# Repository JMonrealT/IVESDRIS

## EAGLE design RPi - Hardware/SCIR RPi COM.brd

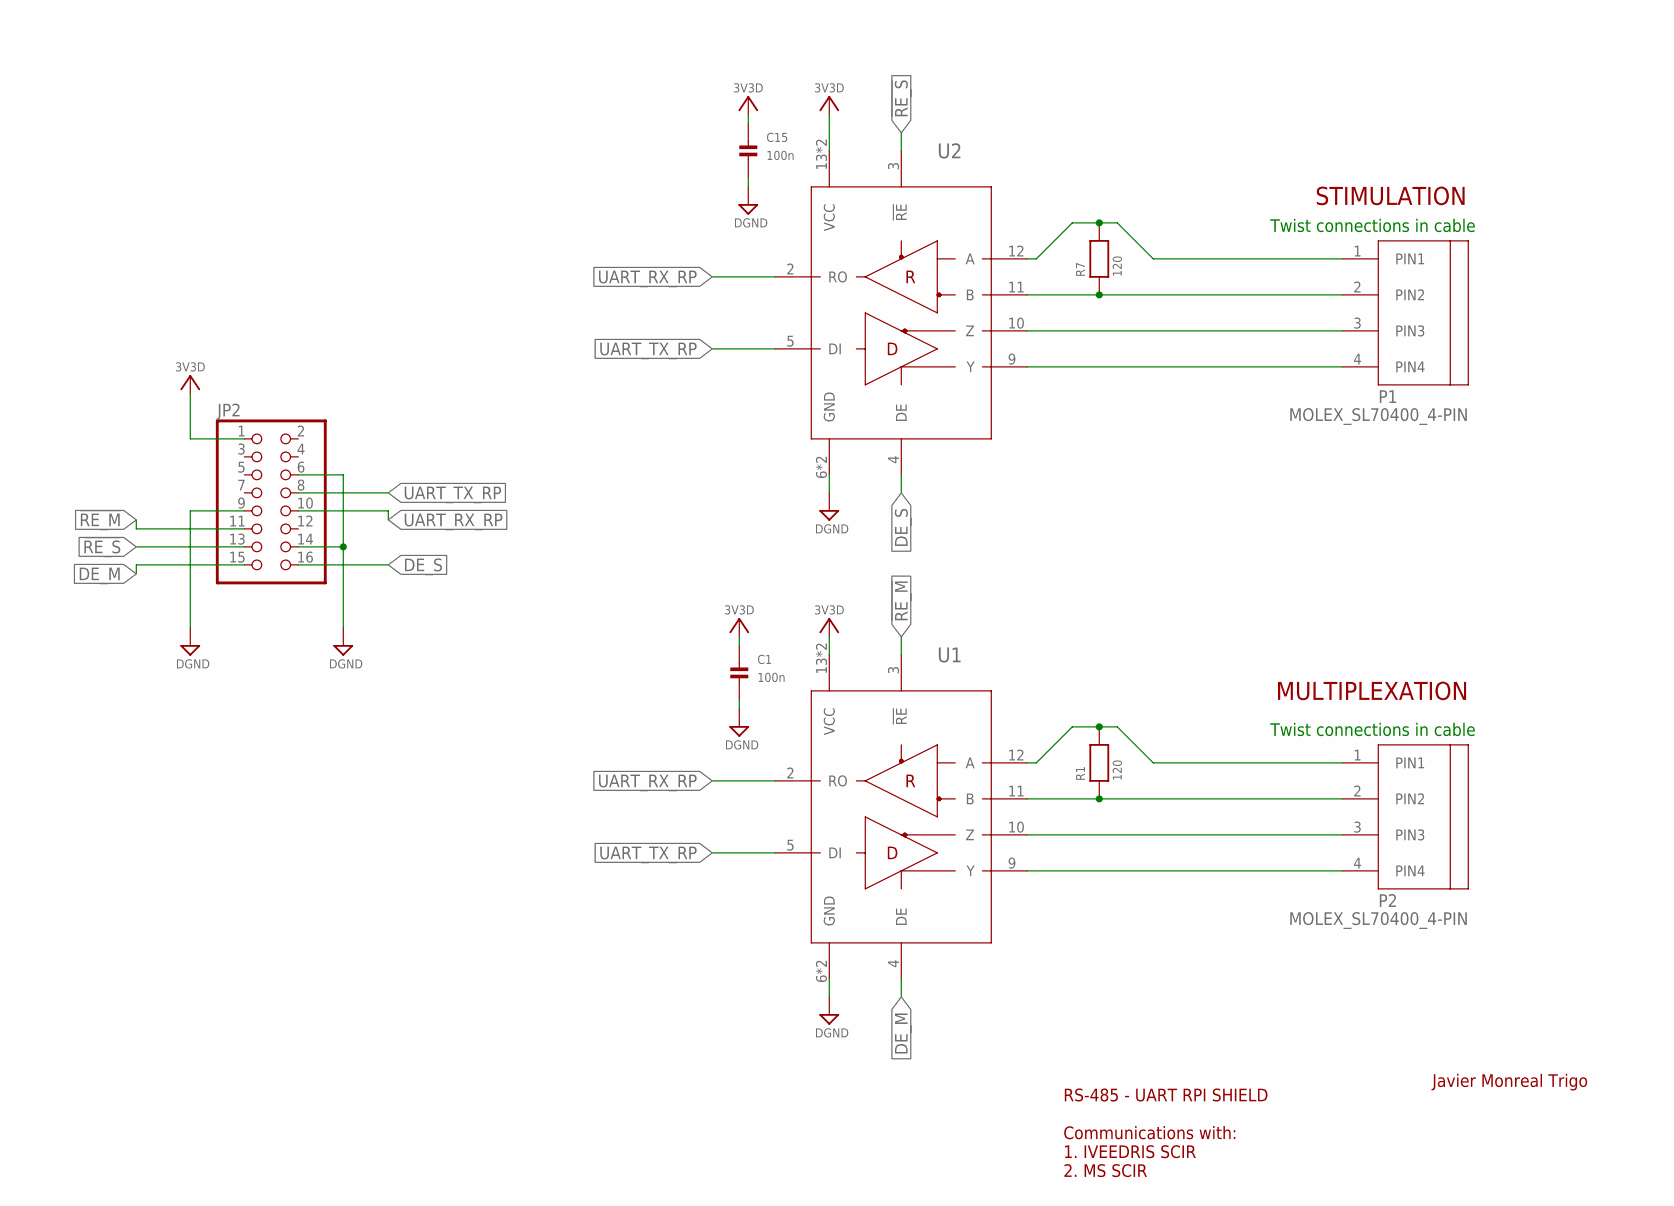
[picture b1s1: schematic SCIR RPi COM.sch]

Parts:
C1, C15: 100n; 0805
JP2: HEADER-2X8; 2X08
P1, P2: MOLEX_SL70400_4-PIN
R1, R7: 120; 0805
U1, U2: MAX3491ECSD+; SO14

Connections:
3V3D: C1.1, C15.1, JP2.1, U1.13 (VCC), U1.14 (VCC), U2.13 (VCC), U2.14 (VCC)
!RE_M: JP2.11, U1.3 (!RE)
!RE_S: JP2.13, U2.3 (!RE)
DE_M: JP2.15, U1.4 (DE)
DE_S: JP2.16, U2.4 (DE)
DGND: C1.2, C15.2, JP2.6, JP2.9, JP2.14, U1.6 (GND), U1.7 (GND), U2.6 (GND), U2.7 (GND)
unnamed: P1.1 (PIN1), R7.2, U2.12 (A)
unnamed: P2.2 (PIN2), R1.1, U1.11 (B)
unnamed: P1.3 (PIN3), U2.10 (Z)
unnamed: P2.1 (PIN1), R1.2, U1.12 (A)
unnamed: P1.4 (PIN4), U2.9 (Y)
unnamed: P2.4 (PIN4), U1.9 (Y)
unnamed: P2.3 (PIN3), U1.10 (Z)
unnamed: P1.2 (PIN2), R7.1, U2.11 (B)
UART_RX_RP: JP2.10, U1.2 (RO), U2.2 (RO)
UART_TX_RP: JP2.8, U1.5 (DI), U2.5 (DI)

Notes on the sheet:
RS-485 - UART RPI SHIELD Communications with: 1. IVEEDRIS SCIR 2. MS SCIR
Twist connections in cable
Javier Monreal Trigo
STIMULATION
MULTIPLEXATION

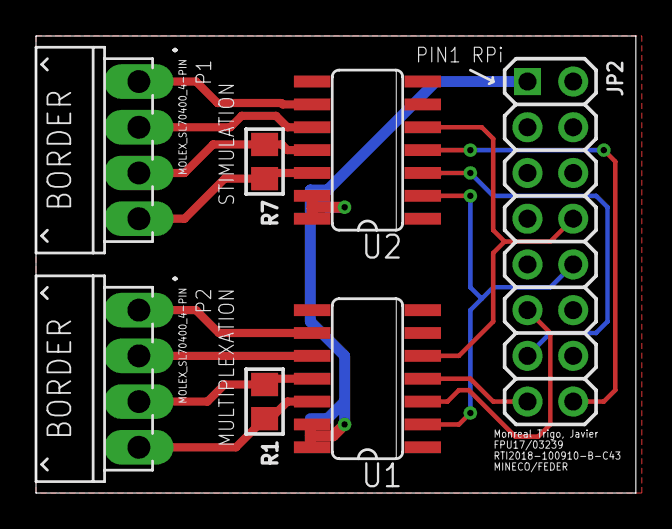
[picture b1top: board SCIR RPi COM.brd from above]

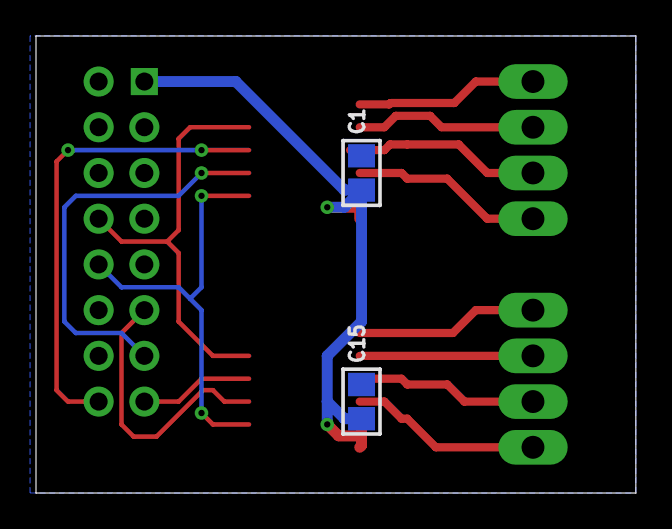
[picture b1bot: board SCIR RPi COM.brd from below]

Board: 2 copper layers, 33.3 x 25.4 mm, 9 parts (2 on the bottom side), 16 nets.

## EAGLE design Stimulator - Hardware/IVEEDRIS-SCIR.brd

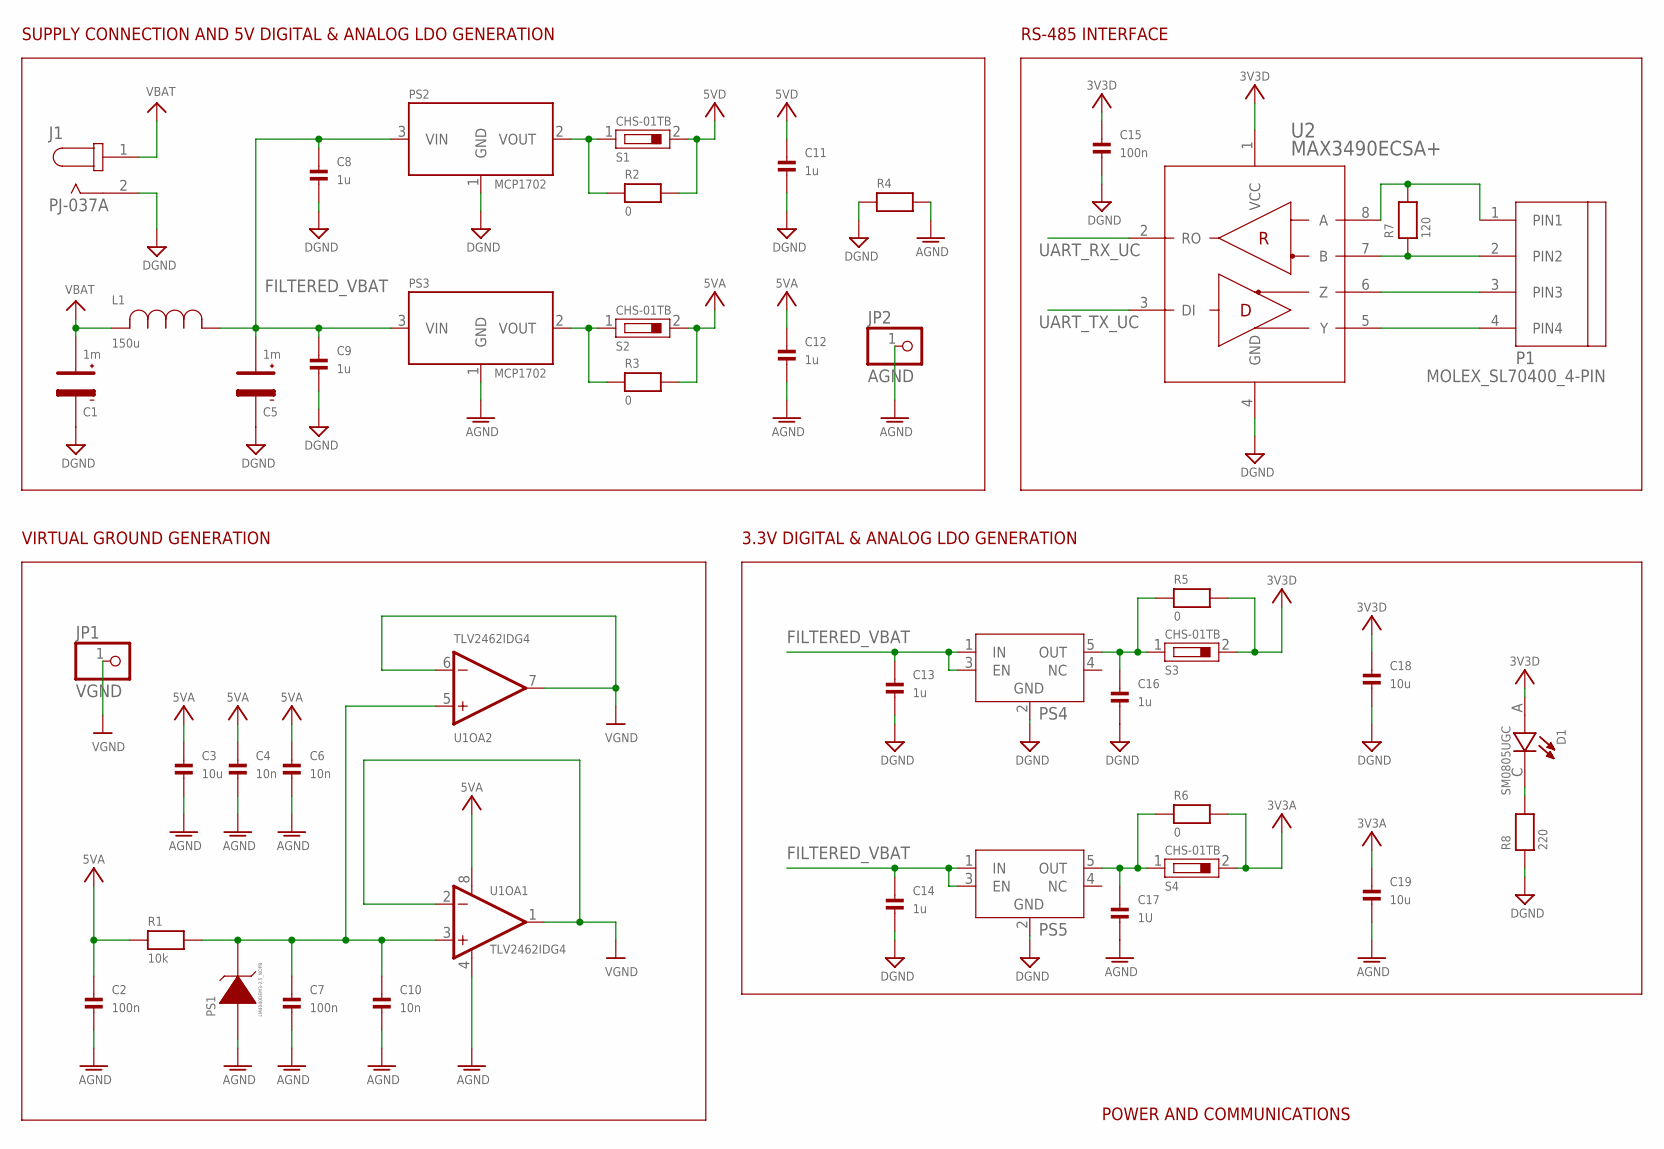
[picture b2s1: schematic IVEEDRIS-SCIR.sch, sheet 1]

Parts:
C1, C5: 1m; CAP_ALUMINIUM
C2, C7, C15: 100n; 0805
C3, C18, C19: 10u; 0805
C4, C6, C10: 10n; 0805
C8, C9, C11, C12, C13, C14, C16: 1u; 0805
C17: 1U; 0805
D1: SM0805UGC; LEDC2012X135N
J1: PJ-037A; CUI_PJ-037A
JP1: VGND; 1X01_OVAL
JP2: AGND; 1X01_OVAL
L1: 150u; IND_PM3308-RC
P1: MOLEX_SL70400_4-PIN
PS1: LM4040DEM3-2.5_NOPB; SOT95P237X112-3N
PS2, PS3: MCP1702; SOT23-A
PS4, PS5: MCP1802T-3302I/OT; TSOT-23_S5
R1: 10k; 0805
R2, R3, R5, R6: 0; 0805
R4: RESISTOR0402; 0402
R7: 120; 0805
R8: 220; 0805
S1, S2, S3, S4: CHS-01TB
U1: TLV2462IDG4; SO8
U2: MAX3490ECSA+; SOIC127P600X175-8N

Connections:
3V3A: C19.1, R6.2, S4.2; also elsewhere on the board
3V3D: C15.1, C18.1, D1.A, R5.2, S3.2, U2.1 (VCC); also elsewhere on the board
5VA: C2.1, C3.1, C4.1, C6.1, C12.1, R1.1, R3.2, S2.2, U1.8 (V+); also elsewhere on the board
5VD: C11.1, R2.2, S1.2; also elsewhere on the board
AGND: C2.2, C3.2, C4.2, C6.2, C7.2, C10.2, C12.2, C17.2, C19.2, JP2.1, PS1.2 (ANODE), PS3.1 (GND), R4.2, U1.4 (V-); also elsewhere on the board
DGND: C1.2, C5.2, C8.2, C9.2, C11.2, C13.2, C14.2, C15.2, C16.2, C18.2, J1.2, PS2.1 (GND), PS4.2 (GND), PS5.2 (GND), R4.1, R8.1, U2.4 (GND); also elsewhere on the board
FILTERED_VBAT: C5.1, C8.1, C9.1, C13.1, C14.1, L1.1, PS2.3 (VIN), PS3.3 (VIN), PS4.1 (IN), PS4.3 (EN), PS5.1 (IN), PS5.3 (EN)
unnamed: PS3.2 (VOUT), R3.1, S2.1
unnamed: P1.4 (PIN4), U2.5 (Y)
unnamed: C7.1, C10.1, PS1.1 (CATHODE), R1.2, U1.3 (+IN), U1.5 (+IN)
unnamed: PS2.2 (VOUT), R2.1, S1.1
unnamed: P1.3 (PIN3), U2.6 (Z)
unnamed: C17.1, PS5.5 (OUT), R6.1, S4.1
unnamed: C16.1, PS4.5 (OUT), R5.1, S3.1
unnamed: D1.C, R8.2
unnamed: P1.2 (PIN2), R7.1, U2.7 (B)
unnamed: P1.1 (PIN1), R7.2, U2.8 (A)
UART_RX_UC: U2.2 (RO); also elsewhere on the board
UART_TX_UC: U2.3 (DI); also elsewhere on the board
VBAT: C1.1, J1.1, L1.2
VGND: JP1.1, U1.1 (OUT), U1.2 (-IN), U1.6 (-IN), U1.7 (OUT); also elsewhere on the board

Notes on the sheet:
POWER AND COMMUNICATIONS
SUPPLY CONNECTION AND 5V DIGITAL & ANALOG LDO GENERATION
VIRTUAL GROUND GENERATION
3.3V DIGITAL & ANALOG LDO GENERATION
RS-485 INTERFACE

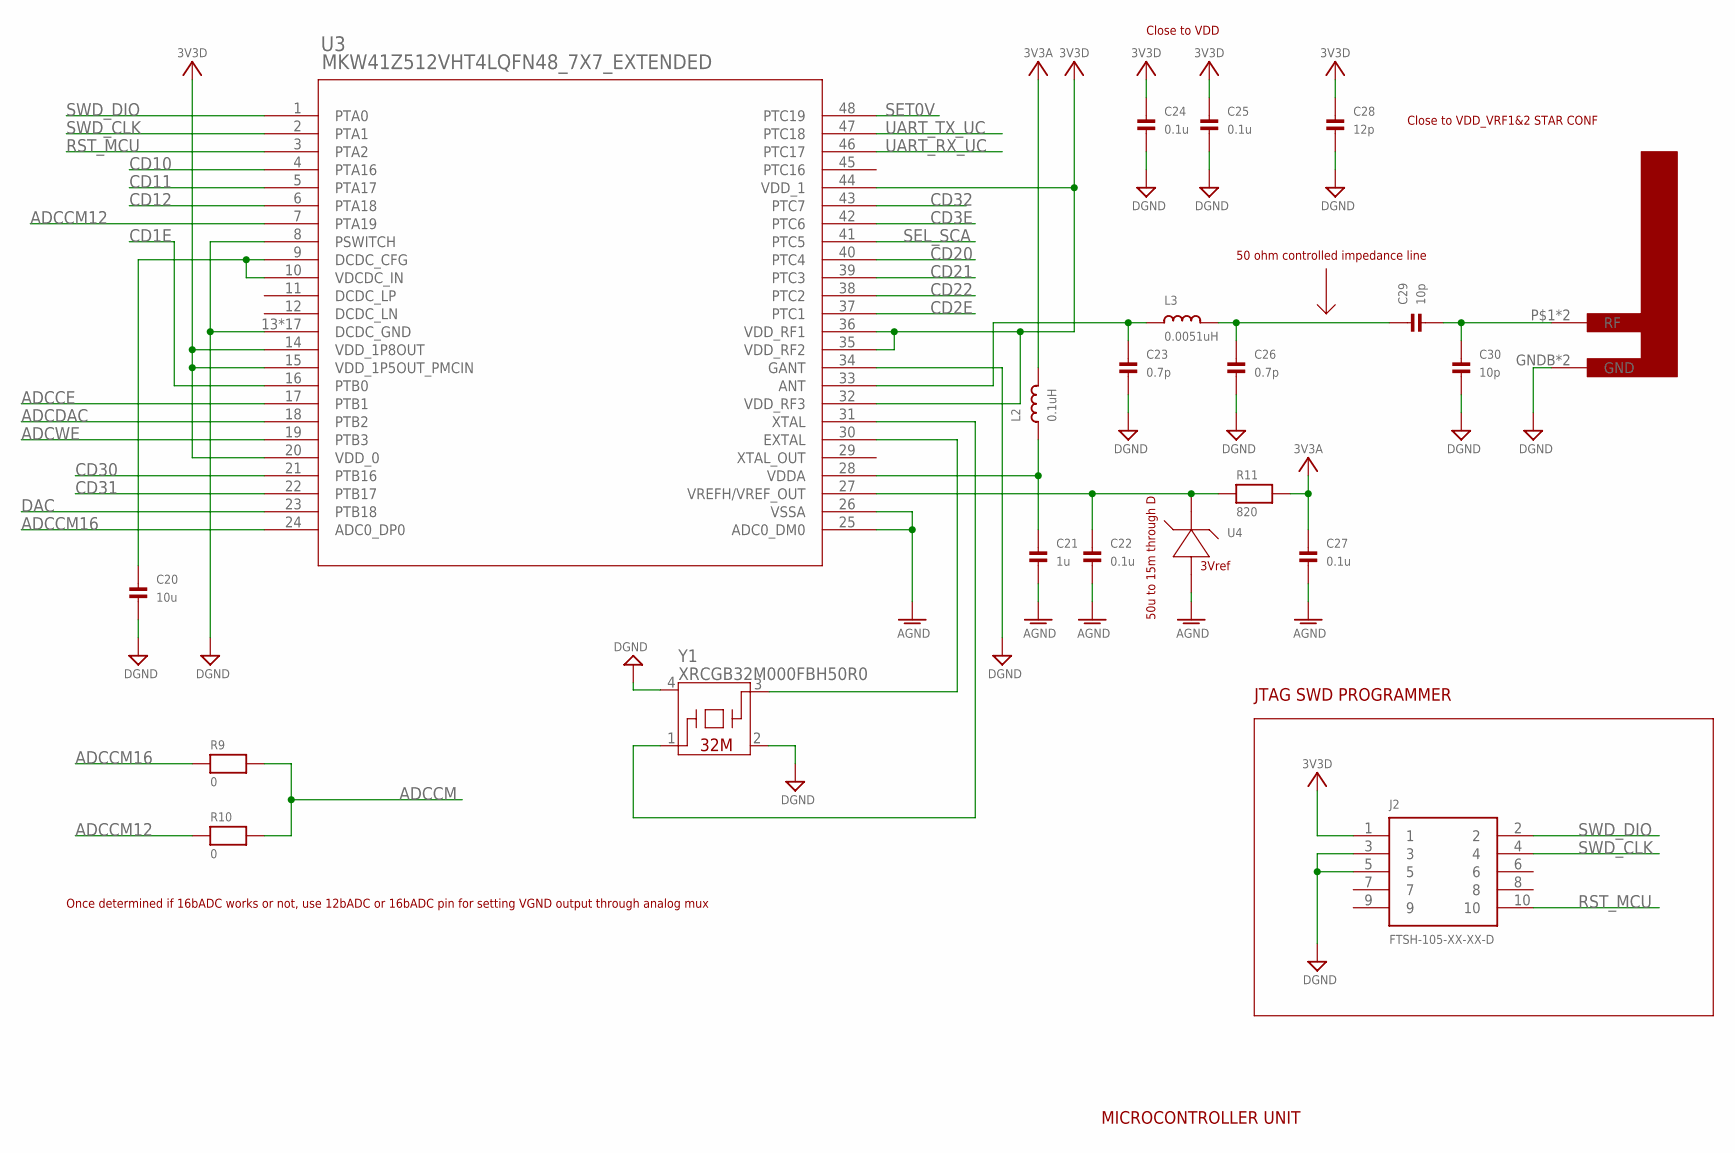
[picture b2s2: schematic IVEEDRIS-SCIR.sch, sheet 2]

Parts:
AE1: F_INVERTED_ANTENNA_2.4G; RF2.4GHZ_FINVERTED_ANTENNA
C20: 10u; 0805
C21: 1u; 0805
C22, C24, C25, C27: 0.1u; 0805
C23, C26: 0.7p; 0805
C28: 12p; 0805
C29, C30: 10p; 0805
J2: FTSH-105-XX-XX-D
L2: 0.1uH; 0805
L3: 0.0051uH; 0805
R9, R10: 0; 0805
R11: 820; 0805
U3: MKW41Z512VHT4LQFN48_7X7_EXTENDED; LQFN48_7X7_EXTENDED
U4: ADR5043BKSZ-REEL7KS_3_ADI-M; KS_3_ADI-M
Y1: XRCGB32M000FBH50R0; XRCGB32_F

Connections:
3V3A: C27.1, L2.2, R11.2; also elsewhere on the board
3V3D: C24.1, C25.1, C28.1, J2.1, U3.14 (VDD_1P8OUT), U3.15 (VDD_1P5OUT_PMCIN), U3.20 (VDD_0), U3.32 (VDD_RF3), U3.35 (VDD_RF2), U3.36 (VDD_RF1), U3.44 (VDD_1); also elsewhere on the board
ADCCE: U3.17 (PTB1); also elsewhere on the board
ADCCM: R9.2, R10.2; also elsewhere on the board
ADCCM12: R10.1, U3.7 (PTA19)
ADCCM16: R9.1, U3.24 (ADC0_DP0)
ADCDAC: U3.18 (PTB2); also elsewhere on the board
ADCWE: U3.19 (PTB3); also elsewhere on the board
AGND: C21.2, C22.2, C27.2, U3.25 (ADC0_DM0), U3.26 (VSSA), U4.2 (V-); also elsewhere on the board
CD1E: U3.16 (PTB0); also elsewhere on the board
CD2E: U3.37 (PTC1); also elsewhere on the board
CD3E: U3.42 (PTC6); also elsewhere on the board
CD10: U3.4 (PTA16); also elsewhere on the board
CD11: U3.5 (PTA17); also elsewhere on the board
CD12: U3.6 (PTA18); also elsewhere on the board
CD20: U3.40 (PTC4); also elsewhere on the board
CD21: U3.39 (PTC3); also elsewhere on the board
CD22: U3.38 (PTC2); also elsewhere on the board
CD30: U3.21 (PTB16); also elsewhere on the board
CD31: U3.22 (PTB17); also elsewhere on the board
CD32: U3.43 (PTC7); also elsewhere on the board
DAC: U3.23 (PTB18); also elsewhere on the board
DGND: AE1.GNDB (GND), AE1.GNDT (GND), C20.2, C23.2, C24.2, C25.2, C26.2, C28.2, C30.2, J2.3, J2.5, U3.8 (PSWITCH), U3.13 (DCDC_GND), U3.34 (GANT), U3.49 (DCDC_GND), U3.50 (DCDC_GND), U3.51 (DCDC_GND), U3.52 (DCDC_GND), U3.53 (DCDC_GND), U3.54 (DCDC_GND), U3.55 (DCDC_GND), U3.56 (DCDC_GND), U3.57 (DCDC_GND), U3.58 (DCDC_GND), U3.59 (DCDC_GND), U3.60 (DCDC_GND), U3.61 (DCDC_GND), U3.62 (DCDC_GND), U3.63 (DCDC_GND), U3.64 (DCDC_GND), Y1.2 (NC_1), Y1.4 (NC_2); also elsewhere on the board
unnamed: C21.1, L2.1, U3.28 (VDDA)
unnamed: C20.1, U3.9 (DCDC_CFG), U3.10 (VDCDC_IN)
unnamed: C22.1, R11.1, U3.27 (VREFH/VREF_OUT), U4.1 (V+)
unnamed: U3.31 (XTAL), Y1.1 (CRYSTAL_1)
unnamed: U3.30 (EXTAL), Y1.3 (CRYSTAL_2)
unnamed: C23.1, L3.1, U3.33 (ANT)
unnamed: C26.1, C29.1, L3.2
unnamed: AE1.P$1 (RF), AE1.RF, C29.2, C30.1
RST_MCU: J2.10, U3.3 (PTA2)
SEL_SCA: U3.41 (PTC5); also elsewhere on the board
SET0V: U3.48 (PTC19); also elsewhere on the board
SWD_CLK: J2.4, U3.2 (PTA1)
SWD_DIO: J2.2, U3.1 (PTA0)
UART_RX_UC: U3.46 (PTC17); also elsewhere on the board
UART_TX_UC: U3.47 (PTC18); also elsewhere on the board

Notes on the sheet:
MICROCONTROLLER UNIT
50 ohm controlled impedance line
Close to VDD
Close to VDD_VRF1&2 STAR CONF
Once determined if 16bADC works or not, use 12bADC or 16bADC pin for setting VGND output through analog mux
JTAG SWD PROGRAMMER
50u to 15m through D

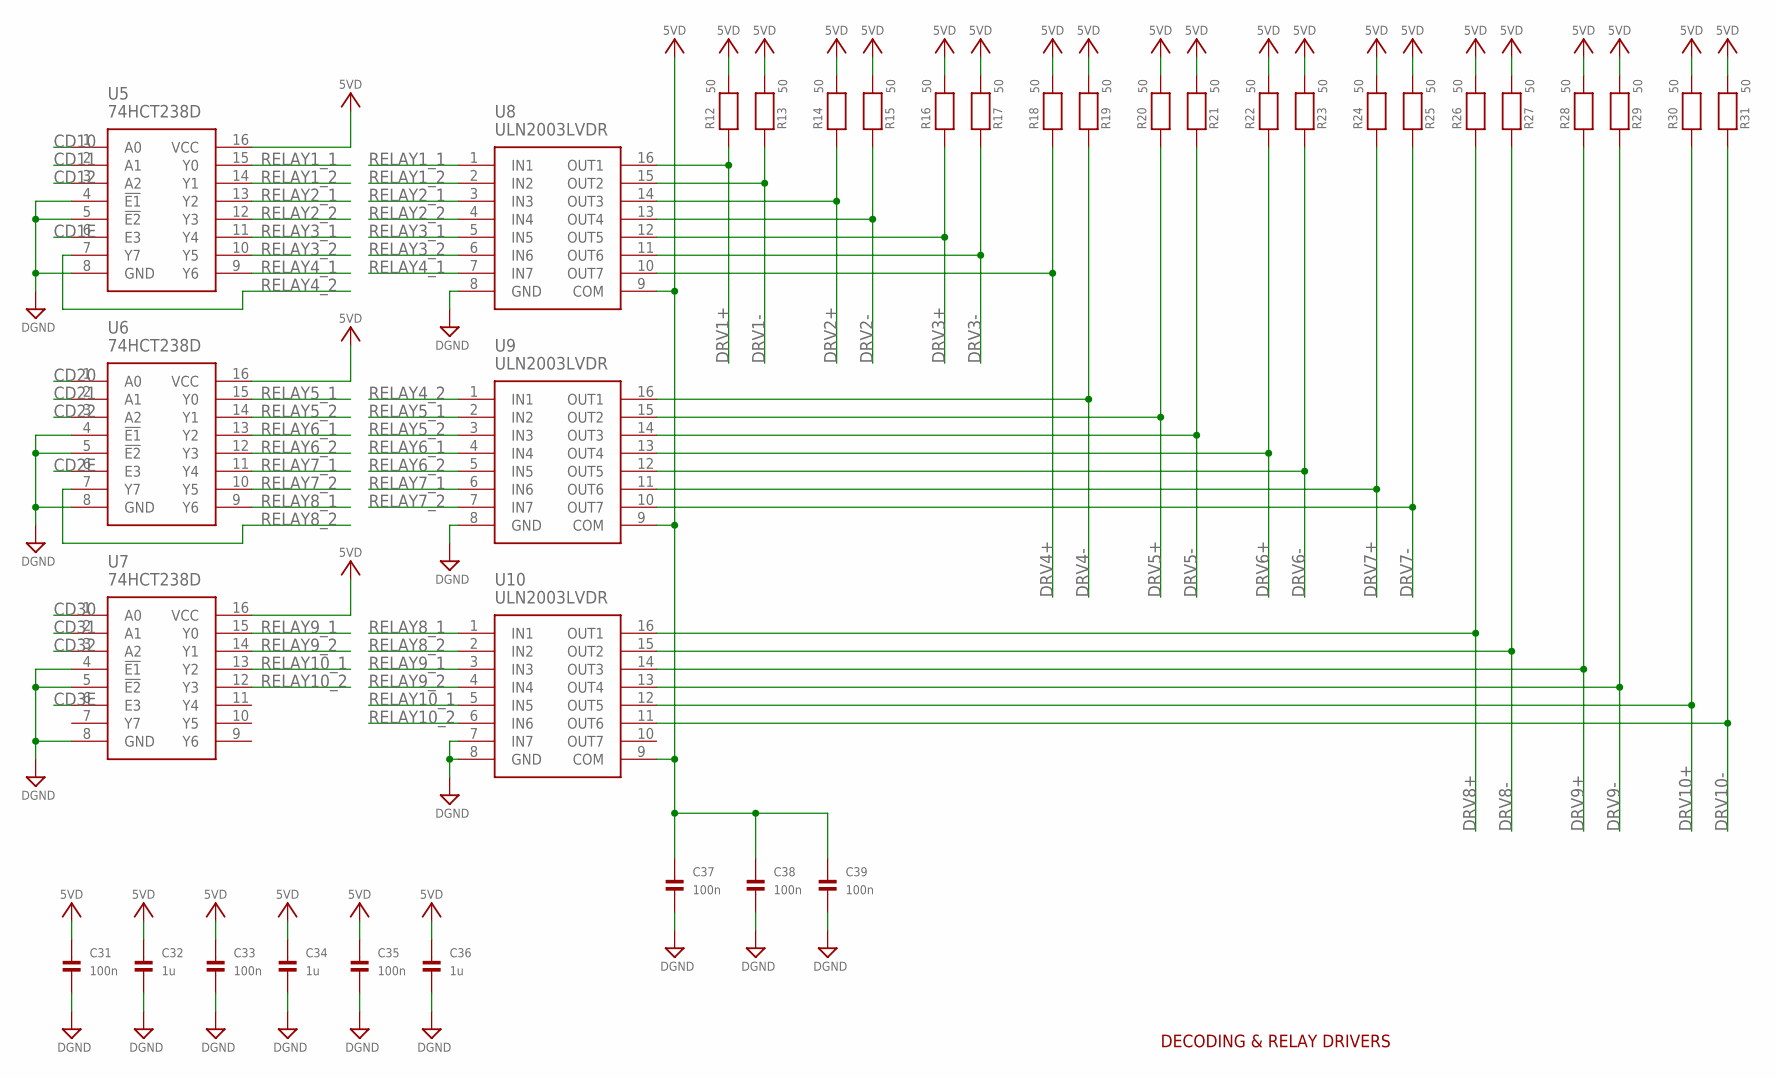
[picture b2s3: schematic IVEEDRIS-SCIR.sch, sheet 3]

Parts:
C31, C33, C35, C37, C38, C39: 100n; 0805
C32, C34, C36: 1u; 0805
R12, R13, R14, R15, R16, R17, R18, R19, R20, R21, R22, R23, R24, R25, R26, R27, R28, R29, R30, R31: 50; 0805
U5, U6, U7: 74HCT238D; SOIC127P600X175-16N
U8, U9, U10: ULN2003LVDR; SOIC127P600X175-16N

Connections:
5VD: C31.1, C32.1, C33.1, C34.1, C35.1, C36.1, C37.1, C38.1, C39.1, R12.2, R13.2, R14.2, R15.2, R16.2, R17.2, R18.2, R19.2, R20.2, R21.2, R22.2, R23.2, R24.2, R25.2, R26.2, R27.2, R28.2, R29.2, R30.2, R31.2, U5.16 (VCC), U6.16 (VCC), U7.16 (VCC), U8.9 (COM), U9.9 (COM), U10.9 (COM); also elsewhere on the board
CD1E: U5.6 (E3); also elsewhere on the board
CD2E: U6.6 (E3); also elsewhere on the board
CD3E: U7.6 (E3); also elsewhere on the board
CD10: U5.1 (A0); also elsewhere on the board
CD11: U5.2 (A1); also elsewhere on the board
CD12: U5.3 (A2); also elsewhere on the board
CD20: U6.1 (A0); also elsewhere on the board
CD21: U6.2 (A1); also elsewhere on the board
CD22: U6.3 (A2); also elsewhere on the board
CD30: U7.1 (A0); also elsewhere on the board
CD31: U7.2 (A1); also elsewhere on the board
CD32: U7.3 (A2); also elsewhere on the board
DGND: C31.2, C32.2, C33.2, C34.2, C35.2, C36.2, C37.2, C38.2, C39.2, U5.4 (!E1), U5.5 (!E2), U5.8 (GND), U6.4 (!E1), U6.5 (!E2), U6.8 (GND), U7.4 (!E1), U7.5 (!E2), U7.8 (GND), U8.8 (GND), U9.8 (GND), U10.7 (IN7), U10.8 (GND); also elsewhere on the board
DRV1+: R12.1, U8.16 (OUT1); also elsewhere on the board
DRV1-: R13.1, U8.15 (OUT2); also elsewhere on the board
DRV2+: R14.1, U8.14 (OUT3); also elsewhere on the board
DRV2-: R15.1, U8.13 (OUT4); also elsewhere on the board
DRV3+: R16.1, U8.12 (OUT5); also elsewhere on the board
DRV3-: R17.1, U8.11 (OUT6); also elsewhere on the board
DRV4+: R18.1, U8.10 (OUT7); also elsewhere on the board
DRV4-: R19.1, U9.16 (OUT1); also elsewhere on the board
DRV5+: R20.1, U9.15 (OUT2); also elsewhere on the board
DRV5-: R21.1, U9.14 (OUT3); also elsewhere on the board
DRV6+: R22.1, U9.13 (OUT4); also elsewhere on the board
DRV6-: R23.1, U9.12 (OUT5); also elsewhere on the board
DRV7+: R24.1, U9.11 (OUT6); also elsewhere on the board
DRV7-: R25.1, U9.10 (OUT7); also elsewhere on the board
DRV8+: R26.1, U10.16 (OUT1); also elsewhere on the board
DRV8-: R27.1, U10.15 (OUT2); also elsewhere on the board
DRV9+: R28.1, U10.14 (OUT3); also elsewhere on the board
DRV9-: R29.1, U10.13 (OUT4); also elsewhere on the board
DRV10+: R30.1, U10.12 (OUT5); also elsewhere on the board
DRV10-: R31.1, U10.11 (OUT6); also elsewhere on the board
RELAY1_1: U5.15 (Y0), U8.1 (IN1)
RELAY1_2: U5.14 (Y1), U8.2 (IN2)
RELAY2_1: U5.13 (Y2), U8.3 (IN3)
RELAY2_2: U5.12 (Y3), U8.4 (IN4)
RELAY3_1: U5.11 (Y4), U8.5 (IN5)
RELAY3_2: U5.10 (Y5), U8.6 (IN6)
RELAY4_1: U5.9 (Y6), U8.7 (IN7)
RELAY4_2: U5.7 (Y7), U9.1 (IN1)
RELAY5_1: U6.15 (Y0), U9.2 (IN2)
RELAY5_2: U6.14 (Y1), U9.3 (IN3)
RELAY6_1: U6.13 (Y2), U9.4 (IN4)
RELAY6_2: U6.12 (Y3), U9.5 (IN5)
RELAY7_1: U6.11 (Y4), U9.6 (IN6)
RELAY7_2: U6.10 (Y5), U9.7 (IN7)
RELAY8_1: U6.9 (Y6), U10.1 (IN1)
RELAY8_2: U6.7 (Y7), U10.2 (IN2)
RELAY9_1: U7.15 (Y0), U10.3 (IN3)
RELAY9_2: U7.14 (Y1), U10.4 (IN4)
RELAY10_1: U7.13 (Y2), U10.5 (IN5)
RELAY10_2: U7.12 (Y3), U10.6 (IN6)

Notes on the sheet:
DECODING & RELAY DRIVERS

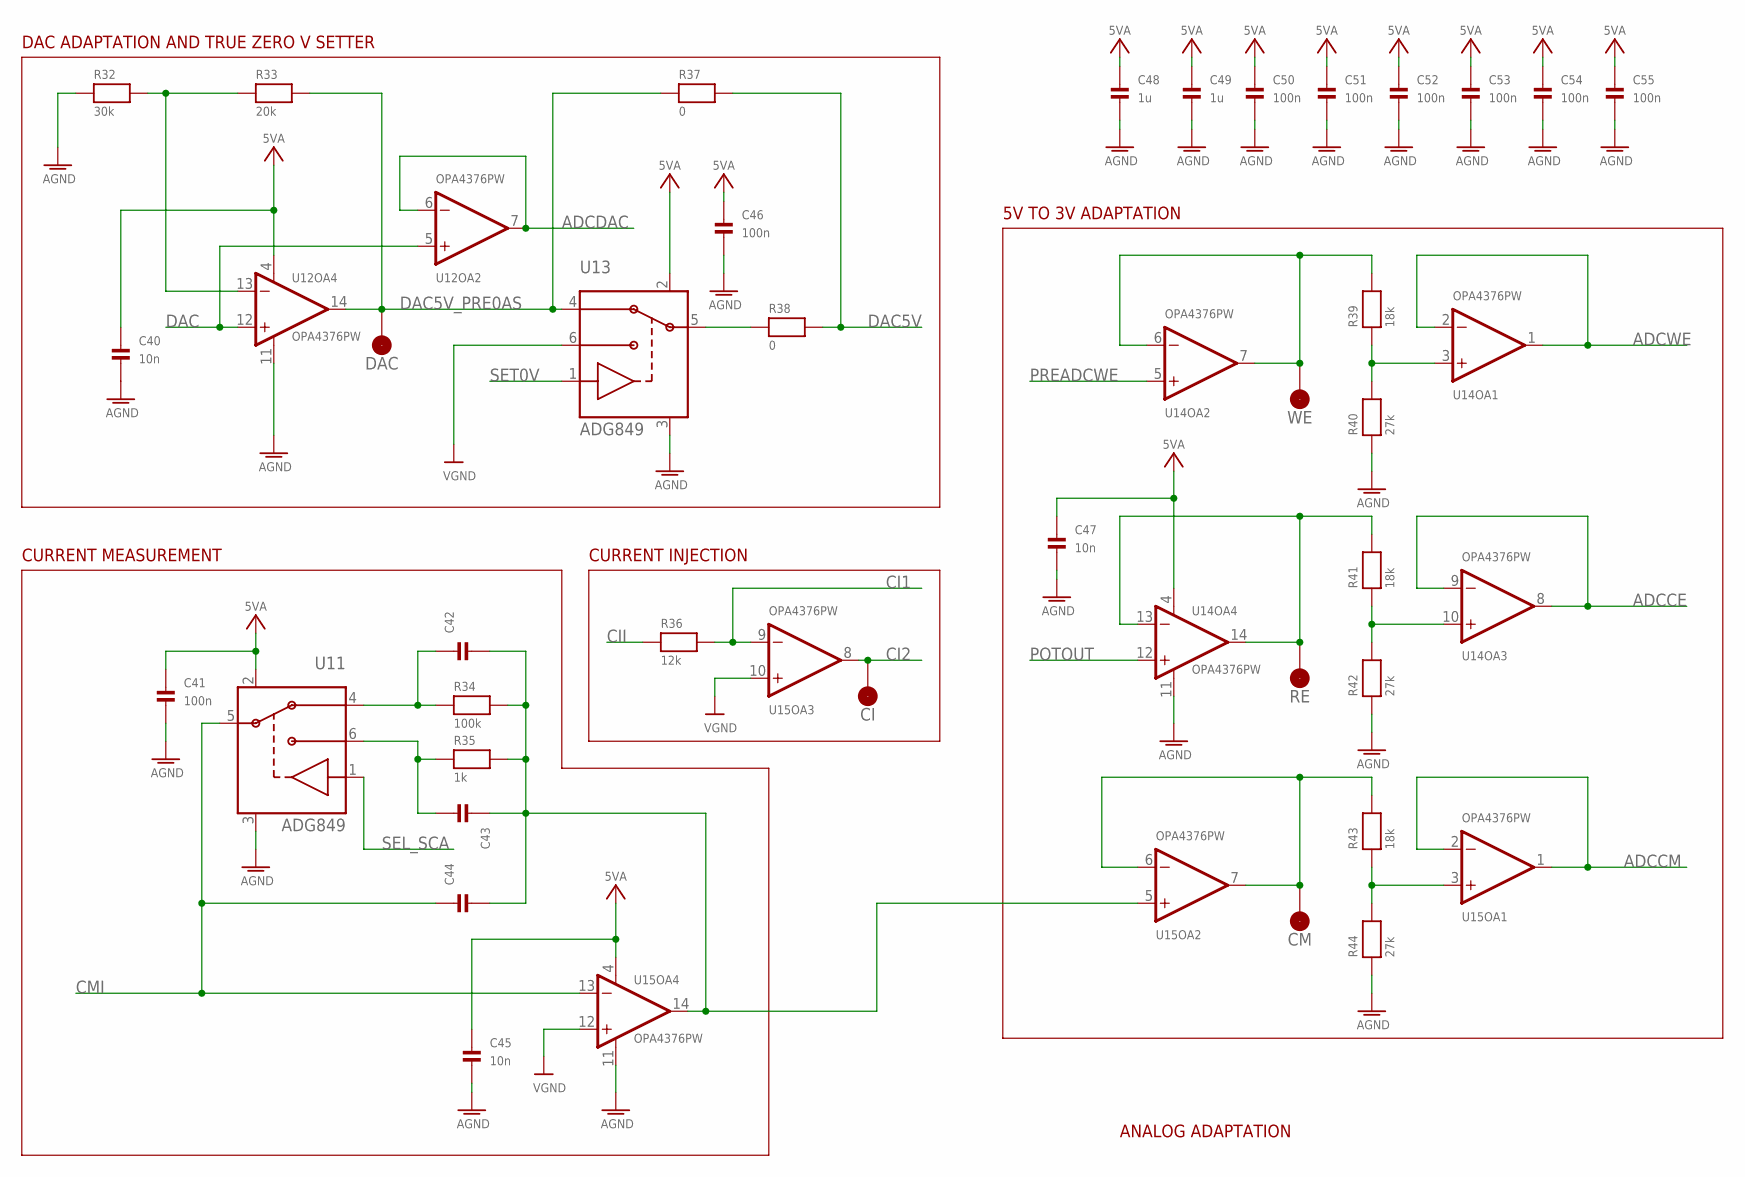
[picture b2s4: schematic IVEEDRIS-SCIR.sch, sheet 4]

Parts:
C40, C45, C47: 10n; 0805
C41, C46, C50, C51, C52, C53, C54, C55: 100n; 0805
C42, C43, C44: CAP_CERAMIC0805; 0805
C48, C49: 1u; 0805
CI: TESTPOINT; NOSOLDERPAD
CM: TESTPOINT; NOSOLDERPAD
DAC: TESTPOINT; NOSOLDERPAD
R32: 30k; 0805
R33: 20k; 0805
R34: 100k; 1206
R35: 1k; 1206
R36: 12k; 1206
R37, R38: 0; 0805
R39, R41, R43: 18k; 0805
R40, R42, R44: 27k; 0805
RE: TESTPOINT; NOSOLDERPAD
U11, U13: ADG849; SC70-6L
U12, U14, U15: OPA4376PW; TSSOP14-NOTHERMALPAD
WE: TESTPOINT; NOSOLDERPAD

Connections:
5VA: C40.1, C41.1, C45.1, C46.1, C47.1, C48.1, C49.1, C50.1, C51.1, C52.1, C53.1, C54.1, C55.1, U11.2 (VDD), U12.4 (V+), U13.2 (VDD), U14.4 (V+), U15.4 (V+); also elsewhere on the board
ADCCE: U14.8 (OUT), U14.9 (-IN); also elsewhere on the board
ADCCM: U15.1 (OUT), U15.2 (-IN); also elsewhere on the board
ADCDAC: U12.6 (-IN), U12.7 (OUT); also elsewhere on the board
ADCWE: U14.1 (OUT), U14.2 (-IN); also elsewhere on the board
AGND: C40.2, C41.2, C45.2, C46.2, C47.2, C48.2, C49.2, C50.2, C51.2, C52.2, C53.2, C54.2, C55.2, R32.1, R40.1, R42.1, R44.1, U11.3 (GND), U12.11 (V-), U13.3 (GND), U14.11 (V-), U15.11 (V-); also elsewhere on the board
CI1: R36.2, U15.9 (-IN); also elsewhere on the board
CI2: CI.P$1, U15.8 (OUT); also elsewhere on the board
CII: R36.1; also elsewhere on the board
CMI: C44.1, U11.5 (D), U15.13 (-IN); also elsewhere on the board
DAC: U12.5 (+IN), U12.12 (+IN); also elsewhere on the board
DAC5V: R37.2, R38.2; also elsewhere on the board
DAC5V_PRE0AS: DAC.P$1, R33.2, R37.1, U12.14 (OUT), U13.4 (S1)
HHHHH: C42.2, C43.2, C44.2, R34.2, R35.2, U15.5 (+IN), U15.14 (OUT)
unnamed: R38.1, U13.5 (D)
unnamed: R41.1, R42.2, U14.10 (+IN)
unnamed: R43.1, R44.2, U15.3 (+IN)
unnamed: R41.2, RE.P$1, U14.13 (-IN), U14.14 (OUT)
unnamed: R39.1, R40.2, U14.3 (+IN)
unnamed: R39.2, U14.6 (-IN), U14.7 (OUT), WE.P$1
unnamed: CM.P$1, R43.2, U15.6 (-IN), U15.7 (OUT)
unnamed: R32.2, R33.1, U12.13 (-IN)
unnamed: C42.1, R34.1, U11.4 (S1)
unnamed: C43.1, R35.1, U11.6 (S2)
POTOUT: U14.12 (+IN); also elsewhere on the board
PREADCWE: U14.5 (+IN); also elsewhere on the board
SEL_SCA: U11.1 (IN); also elsewhere on the board
SET0V: U13.1 (IN); also elsewhere on the board
VGND: U13.6 (S2), U15.10 (+IN), U15.12 (+IN); also elsewhere on the board

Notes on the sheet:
CURRENT MEASUREMENT
DAC ADAPTATION AND TRUE ZERO V SETTER
CURRENT INJECTION
ANALOG ADAPTATION
5V TO 3V ADAPTATION

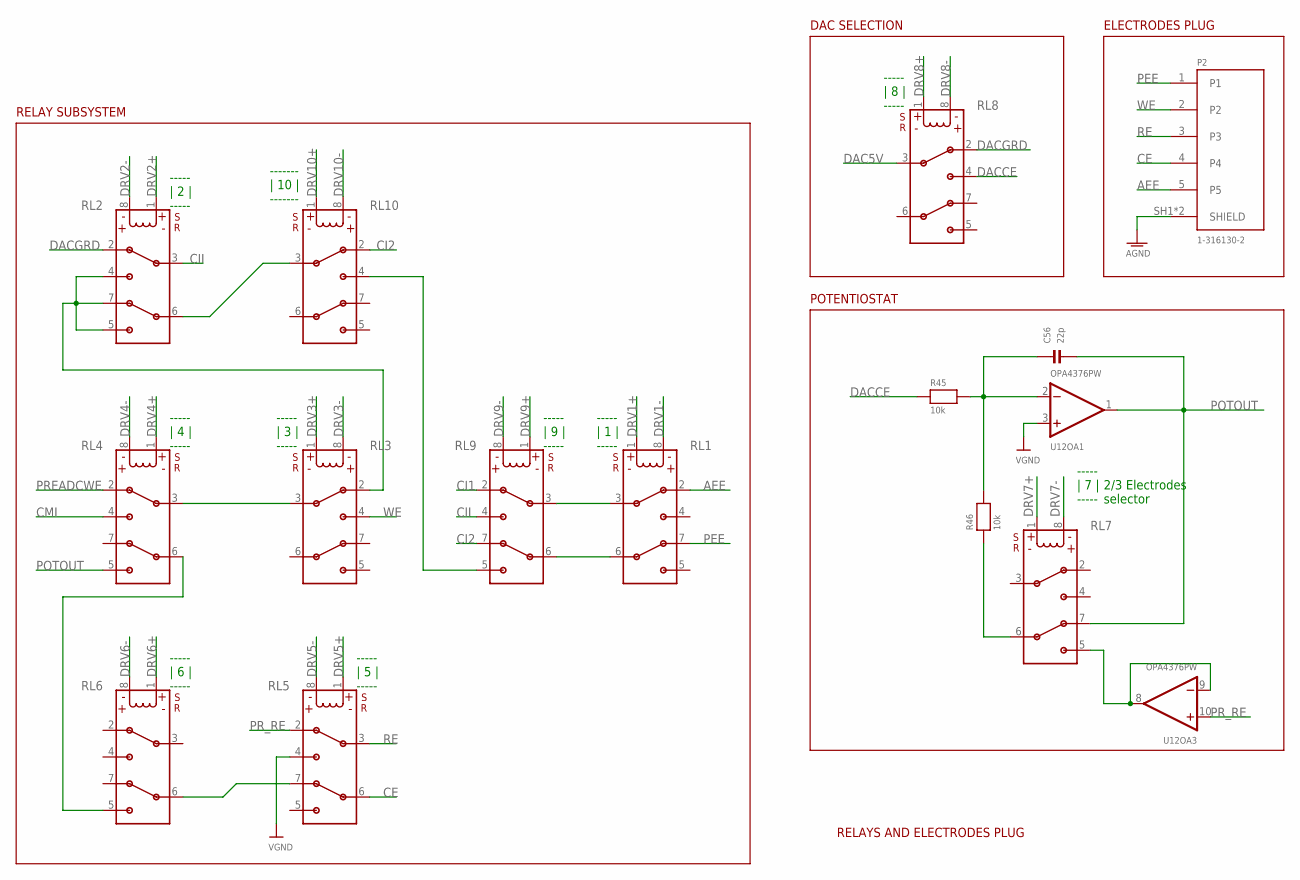
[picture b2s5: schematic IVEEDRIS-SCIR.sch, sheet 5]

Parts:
C56: 22p; 0805
P2: 1-316130-2; TE_1-316130-2
R45, R46: 10k; 0805
RL1, RL2, RL3, RL4, RL5, RL6, RL7, RL8, RL9, RL10: G6KU-2F-Y
U12: OPA4376PW; TSSOP14-NOTHERMALPAD

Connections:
AEE: P2.5, RL1.2
AGND: P2.SH1 (SHIELD), P2.SH2 (SHIELD); also elsewhere on the board
CE: P2.4, RL5.6
CI1: RL9.2; also elsewhere on the board
CI2: RL9.7, RL10.2; also elsewhere on the board
CII: RL2.3, RL9.4; also elsewhere on the board
CMI: RL4.4; also elsewhere on the board
DAC5V: RL8.3; also elsewhere on the board
DACCE: R45.1, RL8.4
DACGRD: RL2.2, RL8.2
DRV1+: RL1.1 (L+); also elsewhere on the board
DRV1-: RL1.8 (L-); also elsewhere on the board
DRV2+: RL2.1 (L+); also elsewhere on the board
DRV2-: RL2.8 (L-); also elsewhere on the board
DRV3+: RL3.1 (L+); also elsewhere on the board
DRV3-: RL3.8 (L-); also elsewhere on the board
DRV4+: RL4.1 (L+); also elsewhere on the board
DRV4-: RL4.8 (L-); also elsewhere on the board
DRV5+: RL5.1 (L+); also elsewhere on the board
DRV5-: RL5.8 (L-); also elsewhere on the board
DRV6+: RL6.1 (L+); also elsewhere on the board
DRV6-: RL6.8 (L-); also elsewhere on the board
DRV7+: RL7.1 (L+); also elsewhere on the board
DRV7-: RL7.8 (L-); also elsewhere on the board
DRV8+: RL8.1 (L+); also elsewhere on the board
DRV8-: RL8.8 (L-); also elsewhere on the board
DRV9+: RL9.1 (L+); also elsewhere on the board
DRV9-: RL9.8 (L-); also elsewhere on the board
DRV10+: RL10.1 (L+); also elsewhere on the board
DRV10-: RL10.8 (L-); also elsewhere on the board
unnamed: RL5.7, RL6.6
unnamed: RL2.6, RL10.3
unnamed: RL1.3, RL9.3
unnamed: RL1.6, RL9.6
unnamed: RL9.5, RL10.4
unnamed: RL2.4, RL2.5, RL2.7, RL3.2
unnamed: RL4.6, RL6.5
unnamed: RL3.3, RL4.3
unnamed: C56.1, R45.2, R46.2, U12.2 (-IN)
PEE: P2.1, RL1.7
POTOUT: C56.2, RL4.5, RL7.7, U12.1 (OUT); also elsewhere on the board
PREADCCE: R46.1, RL7.6
PREADCRE: RL7.5, U12.8 (OUT), U12.9 (-IN)
PREADCWE: RL4.2; also elsewhere on the board
PR_RE: RL5.2, U12.10 (+IN)
RE: P2.3, RL5.3
VGND: RL5.4, U12.3 (+IN); also elsewhere on the board
WE: P2.2, RL3.4

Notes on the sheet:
2/3 Electrodes selector
----- | 7 | -----
----- | 6 | -----
----- | 4 | -----
----- | 2 | -----
----- | 1 | -----
----- | 3 | -----
----- | 5 | -----
----- | 8 | -----
----- | 9 | -----
------- | 10 | -------
RELAY SUBSYSTEM
DAC SELECTION
ELECTRODES PLUG
POTENTIOSTAT
RELAYS AND ELECTRODES PLUG

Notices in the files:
parts and their libraries:
microbuilder: This work is placed in the public domain, and may be freely used for commercial and non-commercial work with the following conditions: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
COPYRIGHT: Copyright (C) 2016 Accelerated Designs. All rights reserved
